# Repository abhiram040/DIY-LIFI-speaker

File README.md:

LiFi(Light fidelity) is a new technology for wireless communication which uses light to to transmit data between two devices.In terms of technology is similar to Wifi.The main difference between Lifi and Wifi is that wifi uses radio frequency to transmit data whereas lifi uses light to transmit data.My project deals with a simple prototype which consists of a lifi transmitter and a receiver which can be built with less than 10$(usd).several advantages like working across higher bandwidth[citation needed], working in areas susceptible to electromagnetic interference (e.g. aircraft cabins, hospitals) and offering higher transmission speeds. The technology is actively being developed by several organizations across the globe.

Youtube Link: https://www.youtube.com/watch?v=fwexLRmhPiE

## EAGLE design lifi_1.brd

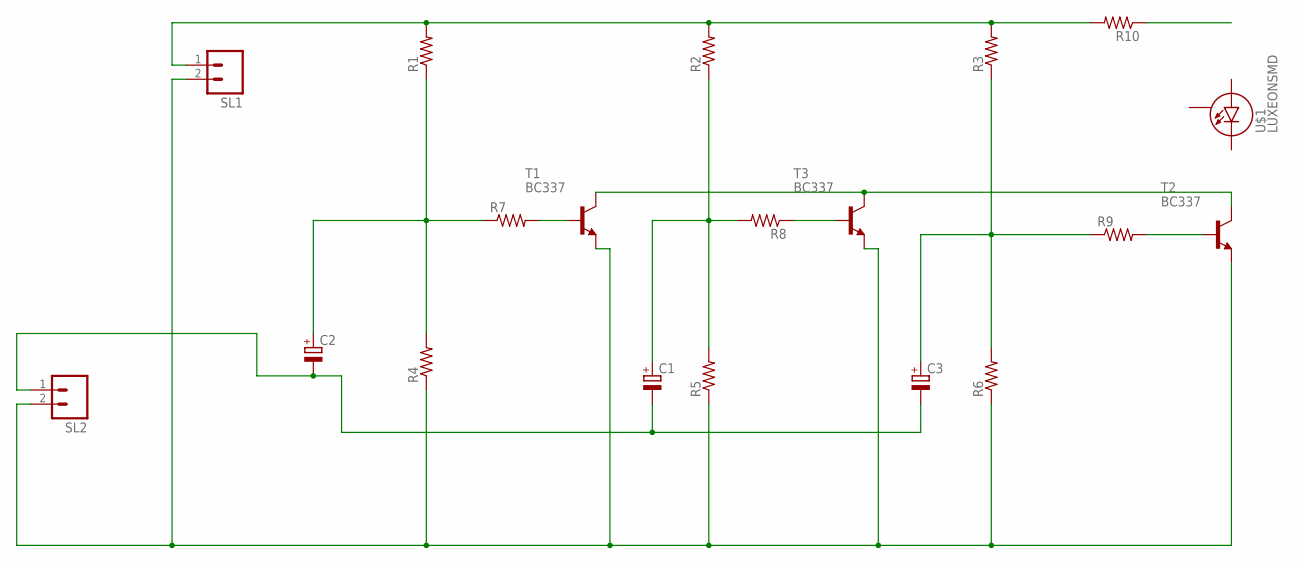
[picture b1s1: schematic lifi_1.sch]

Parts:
C1, C2, C3: CPOL-EUE2,5-6E; E2,5-6E
R1, R2, R3, R4, R5, R6, R7, R8, R9: RESISTOR0207/7; 0207/7
R10: RESISTORPTH-1W; AXIAL-0.6
SL1, SL2: M02; 02P
T1, T2, T3: BC337; TO92
U$1: LUXEONSMD; LUXEON

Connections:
unnamed: R1.2, R2.2, R3.2, R10.P$2 (2), SL1.1
unnamed: C2.+, R1.1, R4.2, R7.1
unnamed: R7.2, T1.2 (B)
unnamed: C1.+, R2.1, R5.2, R8.2
unnamed: R8.1, T3.2 (B)
unnamed: C3.+, R3.1, R6.2, R9.1
unnamed: R9.2, T2.2 (B)
unnamed: T1.3 (C), T2.3 (C), T3.3 (C)
unnamed: C1.-, C2.-, C3.-, SL2.1
unnamed: R4.1, R5.1, R6.1, SL1.2, SL2.2, T1.1 (E), T2.1 (E), T3.1 (E)

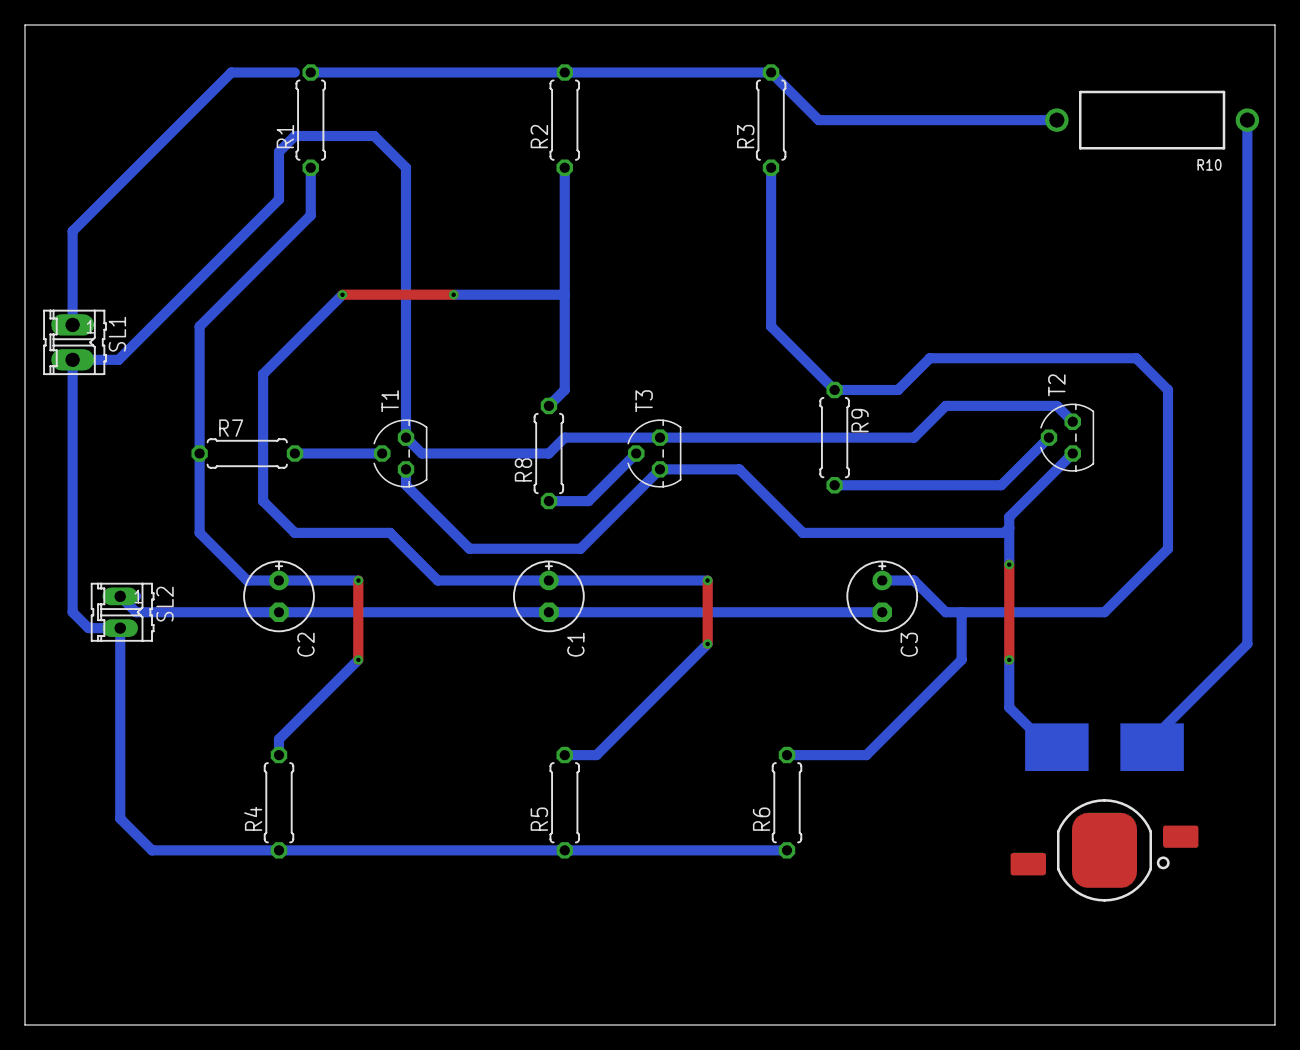
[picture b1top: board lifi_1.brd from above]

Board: 2 copper layers, 100.0 x 80.0 mm, 19 parts (0 on the bottom side), 10 nets.

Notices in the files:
parts and their libraries:
SparkFun-LED: Licensing: Creative Commons ShareAlike 4.0 International - https://creativecommons.org/licenses/by-sa/4.0
